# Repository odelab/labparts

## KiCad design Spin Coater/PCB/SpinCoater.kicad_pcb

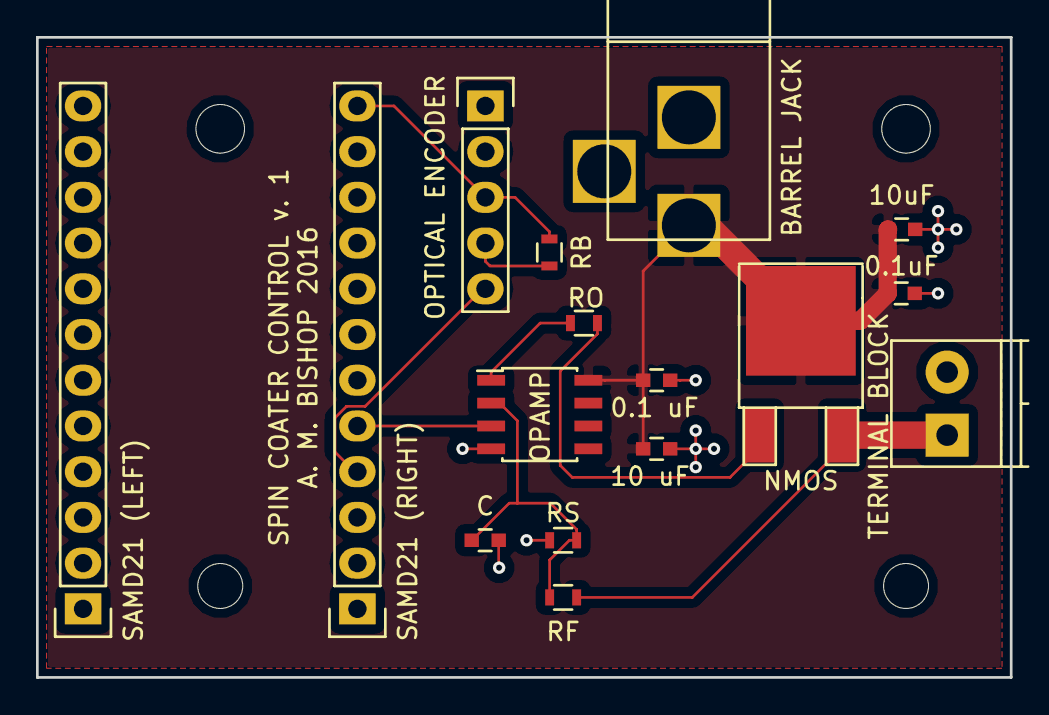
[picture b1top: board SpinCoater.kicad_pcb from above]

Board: 2 copper layers, 54.1 x 35.6 mm, 16 parts (0 on the bottom side), 10 nets.

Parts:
0.1uF: 0.1 uF; C_0603
10uF: 10 uF; C_0603
BARREL JACK: BARREL_JACK; BARREL_JACK_round
C: C; C_0603
C4: 10 uF; C_0603
C5: 0.1 uF; C_0603
NMOS: Q_PMOS_GDS; TO-252-2Lead
OPAMP: MCP6002; SOIC-8_3.9x4.9mm_Pitch1.27mm
OPTICAL ENCODER: OPTICAL ENCODER; Socket_Strip_Straight_1x05
RB: R; R_0603
RF: 10k; R_0603
RO: 10; R_0603
RS: 1k; R_0603
SAMD21 (LEFT): SAMD21 (LEFT); Pin_Header_Straight_1x12
SAMD21 (RIGHT): SAMD21 (RIGHT); Pin_Header_Straight_1x12
TERMINAL BLOCK: TERMINAL BLOCK; TerminalBlock_Pheonix_PT-3.5mm_2pol

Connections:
/Power_In: 0.1uF.1, 10uF.1, BARREL JACK.1, C4.1, C5.1, NMOS.2, OPAMP.8
/Power_Motor: NMOS.3, RF.1, TERMINAL BLOCK.1
GND: 0.1uF.2, 10uF.2, BARREL JACK.2, C.2, C4.2, C5.2, OPAMP.4, OPTICAL ENCODER.1, OPTICAL ENCODER.2, RS.2, SAMD21 (RIGHT).11, TERMINAL BLOCK.2
unnamed: C.1, OPAMP.2, RF.2, RS.1
unnamed: OPTICAL ENCODER.5, SAMD21 (RIGHT).4
unnamed: OPAMP.3, SAMD21 (RIGHT).5
unnamed: OPTICAL ENCODER.3, RB.2, SAMD21 (RIGHT).12
unnamed: OPTICAL ENCODER.4, RB.1
unnamed: NMOS.1, RO.1
unnamed: OPAMP.1, RO.2

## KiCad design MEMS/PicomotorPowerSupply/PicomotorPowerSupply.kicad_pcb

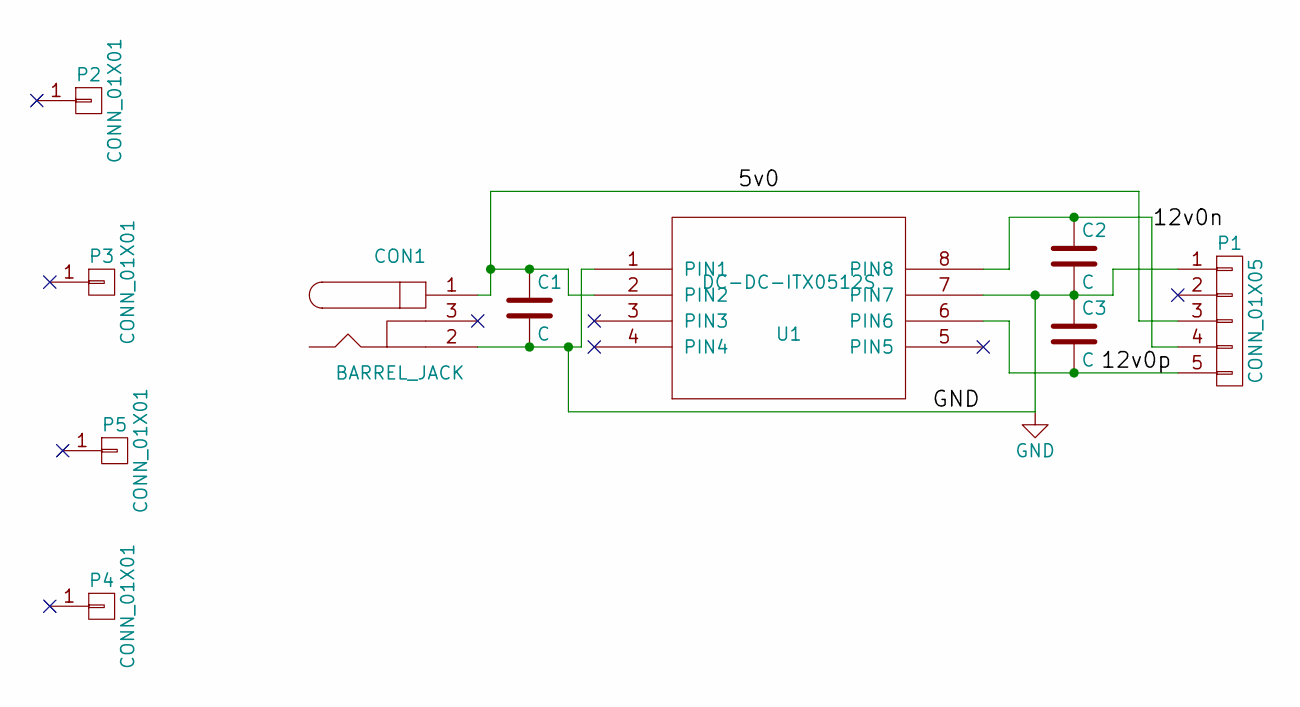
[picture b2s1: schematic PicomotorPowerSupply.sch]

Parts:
C1, C2, C3: C; C_Radial_D6.3_L11.2_P2.5
CON1: BARREL_JACK; BARREL_JACK_round
P1: CONN_01X05; SDS-50J
P2, P3, P4, P5: CONN_01X01; MountingHole_6-5mm
U1: DC-DC-ITX0512S; ITX0512S

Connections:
/5v0: C1.1, CON1.1, P1.3, U1.2 (PIN2)
/12v0n: C2.1, P1.4, U1.8 (PIN8)
/12v0p: C3.2, P1.5, U1.6 (PIN6)
GND: C1.2, C2.2, C3.1, CON1.2, P1.1, U1.1 (PIN1), U1.7 (PIN7)

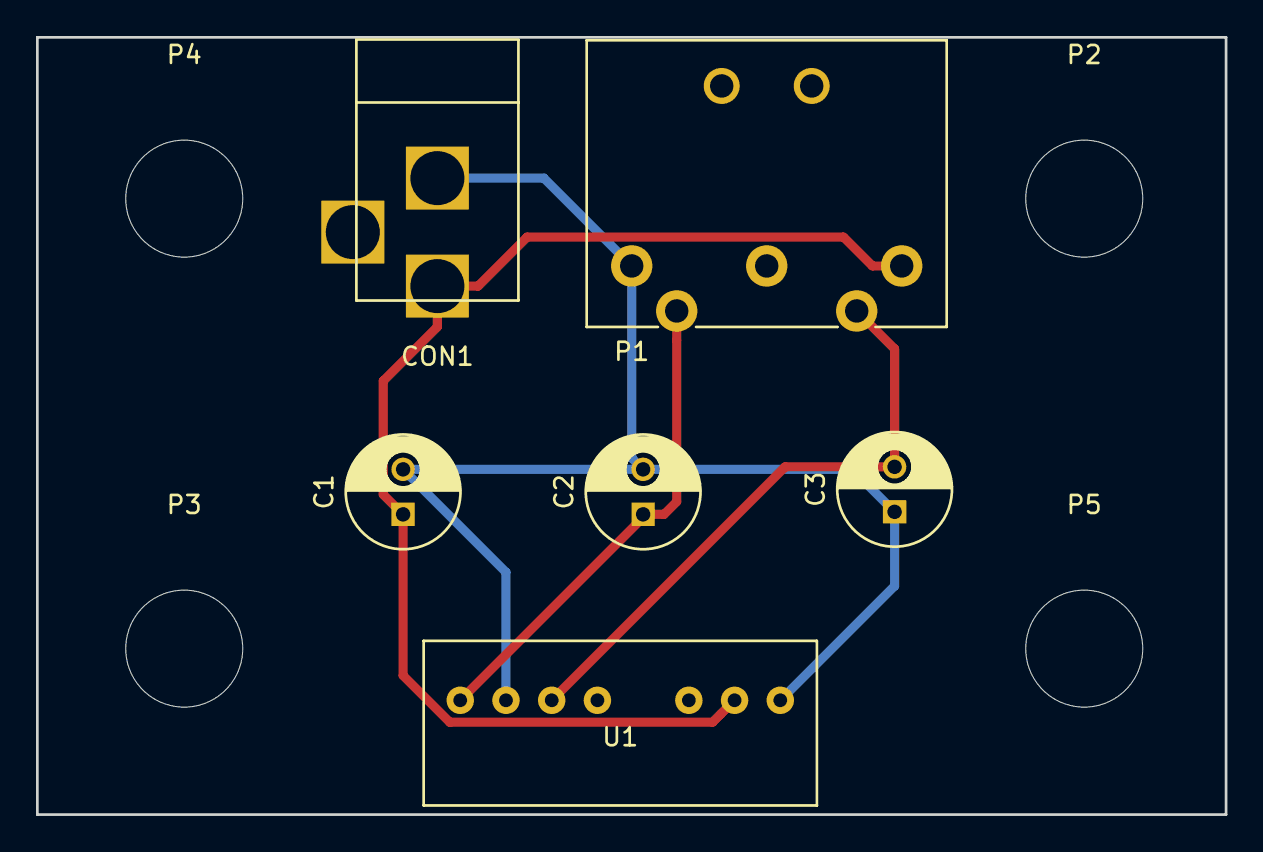
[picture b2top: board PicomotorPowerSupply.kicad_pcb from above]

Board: 2 copper layers, 66.0 x 43.2 mm, 10 parts (0 on the bottom side), 4 nets.

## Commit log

2016-06-01 Added file system
2016-06-02 Added Picomotor Power Supply
2016-06-02 Added mini chuck .step
2016-06-09 Added Solar Sensor
2016-06-10 Found more op amps
2016-07-21 Exported .step files for more components
2016-07-27 Updated Docs
    as well as PCB for spin coater
2016-07-27 made furnace endcap
2016-07-27 Feedthrough docs
2016-07-28 Furnace End Cap
2016-07-28 Located all related files
2017-01-24 new optical encoder for smaller shaft
2017-05-31 Added electrode testing for dielectrophoresis
    These are early versions of the micro pump electrodes
2017-06-01 added new MEMS components
2017-06-12 SMA Feedthrough and Droplet Molds
2017-06-12 Updated mold file
2017-06-22 Evaporator drawings and new electrode GDS
2017-07-14 uploaded images from ODE computer
2017-07-14 More mold test images uploaded
2017-07-18 raster molds measured
2017-07-20 New droplet images
2017-07-20 Interdigitated electrode GDS files
2017-07-21 New mold, new droplets
2017-07-22 electrowetting data from prober
2017-07-23 Photos of FluoroPel film failures
2017-07-24 Photos of droplets
2017-07-25 poster photos
